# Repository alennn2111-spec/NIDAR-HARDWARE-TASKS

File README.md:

# NIDAR 0–10V Analog Signal Generator

**An adjustable 0–10V analog output stage, taken from first-principles research through simulation to PCB layout.**

Developed by the hardware team for the **NIDAR** competition.

---

## Overview

Many industrial controllers, drives and sensors expect a standard 0–10V analog control signal. This project designs a compact, adjustable signal source that produces that range from a digital input, and documents every engineering decision on the way: why the topology was chosen, how the numbers were derived, how the design behaves in simulation, and how it was laid out as a board.

The repository is both a design record and a reproducible starting point. Anyone should be able to open the files, follow the reasoning, and rebuild or extend the design.

## Design Workflow

```
Research  →  Block Diagram  →  Calculations  →  Simulation  →  PCB Layout  →  Fabrication  →  Validation
 (done)         (done)           (done)          (done)          (done)        (pending)       (pending)
```

## Repository Contents

| Path | Stage | Description |
| --- | --- | --- |
| [`Task1_0-10V_Signal.html`](Task1_0-10V_Signal.html) | Introduction | What a 0–10V signal is and why it is used |
| [`Task2_0-10V_Circuit_Research.html`](Task2_0-10V_Circuit_Research.html) | Research | Survey of candidate circuit approaches and trade-offs |
| [`Task3_0-10V_Block_Diagram.html`](Task3_0-10V_Block_Diagram.html) | Architecture | System-level block diagram of the signal chain |
| [`Task4_0-10V_Electrical_Calculations.html`](Task4_0-10V_Electrical_Calculations.html) | Analysis | Component selection and electrical calculations |
| [`DAC_0-10V.asc`](DAC_0-10V.asc) | Simulation | First LTspice iteration of the circuit |
| [`DAC_0-10V final simulation.asc`](DAC_0-10V%20final%20simulation.asc) | Simulation | Final, refined LTspice model |
| [`pcb.kicad_pcb`](pcb.kicad_pcb) | Hardware | KiCad board layout for the final circuit |

## Getting Started

**Read the documentation**
Download the repository (or clone it) and open the `Task*.html` files in any web browser. They are best read in order, Task 1 through Task 4.

```bash
git clone https://github.com/alennn2111-spec/NIDAR-HARDWARE-TASKS.git
cd NIDAR-HARDWARE-TASKS
```

**Run the simulation**
1. Install [LTspice](https://www.analog.com/en/resources/design-tools-and-calculators/ltspice-simulator.html).
2. Open `DAC_0-10V final simulation.asc`.
3. Run the simulation and probe the output node to inspect the 0–10V behaviour.

`DAC_0-10V.asc` is kept for reference so the evolution of the design is visible.

**Inspect the PCB**
1. Install [KiCad](https://www.kicad.org/).
2. Open `pcb.kicad_pcb` in the PCB Editor to review the layout, placement and routing.

## Tools

| Tool | Used for |
| --- | --- |
| LTspice | Circuit simulation and analysis |
| KiCad | PCB layout |
| HTML / CSS | Technical documentation |

## Project Status

| Milestone | Status |
| --- | --- |
| Initial and circuit research | Complete |
| System block diagram | Complete |
| Electrical calculations | Complete |
| LTspice simulation | Complete |
| PCB layout | Complete |
| PCB fabrication | Pending |
| Hardware assembly | Pending |
| Physical testing and validation | Pending |

## Roadmap

- Fabricate the PCB and assemble the first prototype
- Measure output accuracy, linearity and noise on the bench
- Compare measured results against the simulation
- Feed findings back into a revised layout if needed

## Contributing

Suggestions, corrections and design reviews are welcome. Please open an issue describing the change, or submit a pull request with a short explanation of what it improves.

## Author

**alennn2111-spec**, NIDAR hardware team.

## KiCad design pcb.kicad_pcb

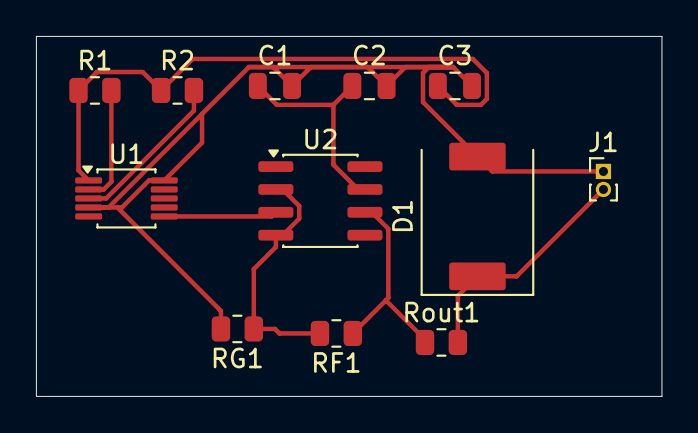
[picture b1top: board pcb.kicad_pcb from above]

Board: 2 copper layers, 34.8 x 20.0 mm, 12 parts (0 on the bottom side), 9 nets.

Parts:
C1: 0.1u; C_0805_2012Metric
C2: 10u; C_0805_2012Metric
C3: 100n; C_0805_2012Metric
D1: D_TVS; ST_D_SMC
J1: Conn_01x02_Pin; PinHeader_1x02_P1.00mm_Vertical
R1, R2: 4.7k; R_0805_2012Metric
RF1: 20.3k; R_0805_2012Metric
RG1: 10k; R_0805_2012Metric
Rout1: 100; R_0805_2012Metric
U1: MCP4728; MSOP-10_3x3mm_P0.5mm
U2: OPA197xD; SOIC-8_3.9x4.9mm_P1.27mm

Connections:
/DAC_OUT: U1.6 (VOUTA), U2.3 (+)
/SCL: R1.2, U1.2 (SCL)
/SDA: R2.2, U1.3 (SDA)
/Vout: D1.1 (A1), J1.2, Rout1.2
GND: C1.2, C2.2, C3.2, D1.2 (A2), J1.1, RG1.2, U1.4 (~LDAC), U1.10 (VSS)
unnamed: RF1.1, Rout1.1, U2.6
unnamed: C3.1, R1.1, R2.1, U1.1 (VDD)
unnamed: RF1.2, RG1.1, U2.2 (-), U2.4 (V-)
unnamed: C1.1, C2.1, U2.7 (V+)
